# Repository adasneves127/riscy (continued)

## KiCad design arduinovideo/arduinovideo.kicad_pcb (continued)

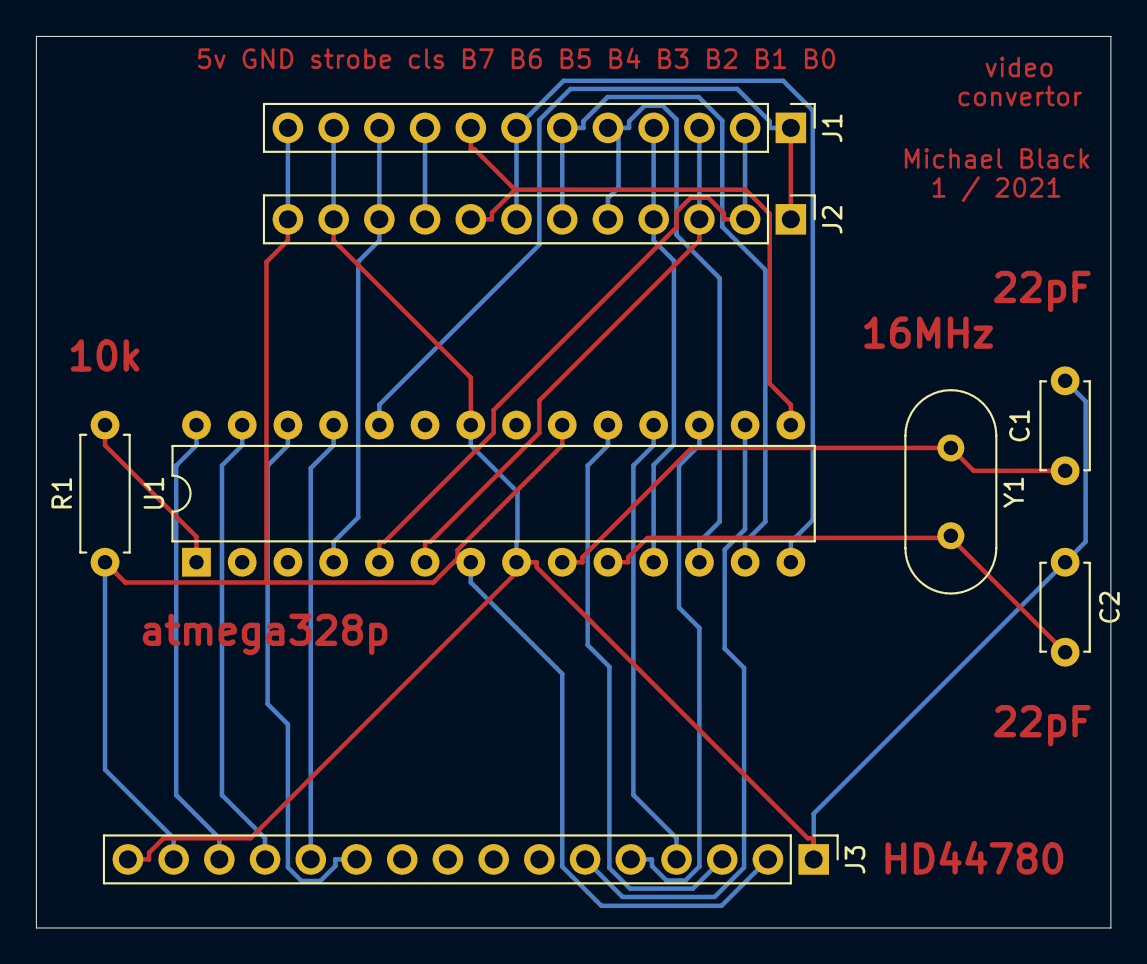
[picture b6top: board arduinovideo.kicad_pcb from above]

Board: 2 copper layers, 59.7 x 49.5 mm, 8 parts (0 on the bottom side), 23 nets.

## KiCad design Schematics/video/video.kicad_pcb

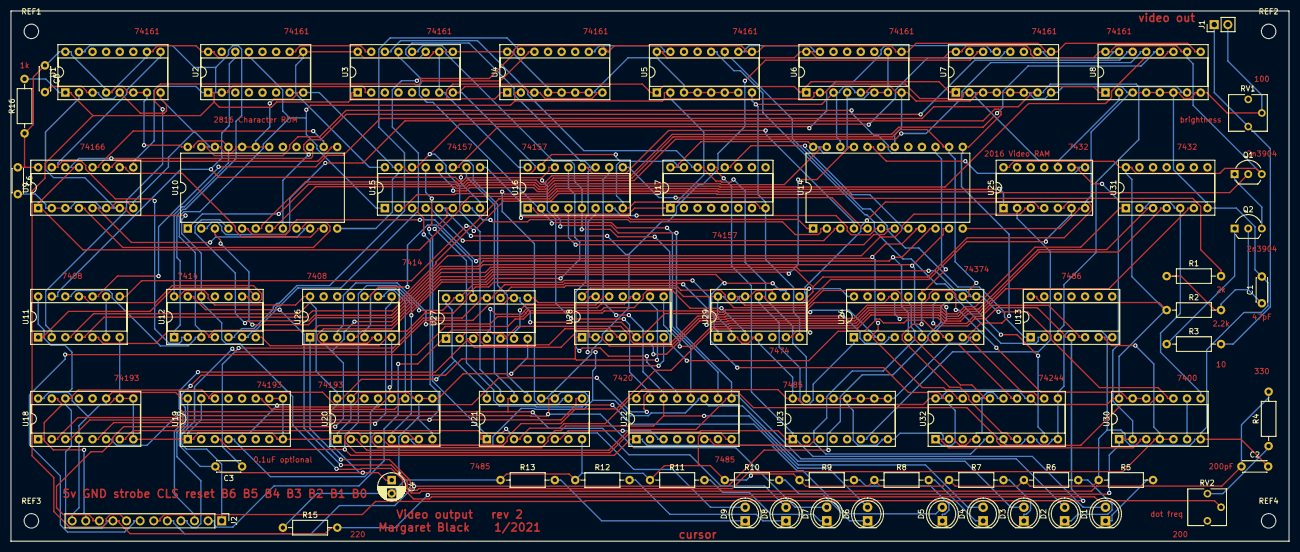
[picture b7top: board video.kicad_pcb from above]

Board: 2 copper layers, 238.8 x 99.1 mm, 72 parts (0 on the bottom side), 119 nets.

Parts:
C1: 47pF; C_Disc_D4.3mm_W1.9mm_P5.00mm
C2: 200pF; C_Disc_D4.3mm_W1.9mm_P5.00mm
C3, C5, C6: 0.1uF; C_Disc_D4.3mm_W1.9mm_P5.00mm
C4: CP; CP_Radial_D5.0mm_P2.50mm
D1, D2, D3, D4, D5, D6, D7, D8, D9: LED; LED_D5.0mm
J1: video_out; PinHeader_1x02_P2.54mm_Vertical
J2: Conn_01x12_Female; PinHeader_1x12_P2.54mm_Vertical
Q1, Q2: 2N3904; TO-92_Inline_Wide
R1: 2k; R_Axial_DIN0207_L6.3mm_D2.5mm_P10.16mm_Horizontal
R2: 2.2k; R_Axial_DIN0207_L6.3mm_D2.5mm_P10.16mm_Horizontal
R3: 10; R_Axial_DIN0207_L6.3mm_D2.5mm_P10.16mm_Horizontal
R4: 330; R_Axial_DIN0207_L6.3mm_D2.5mm_P10.16mm_Horizontal
R5, R6, R7, R8, R9, R10, R11, R12, R13, R16: 1k; R_Axial_DIN0207_L6.3mm_D2.5mm_P10.16mm_Horizontal
R15: 220; R_Axial_DIN0207_L6.3mm_D2.5mm_P10.16mm_Horizontal
REF1, REF2, REF3, REF4: MountingHole_2.7mm_M2.5
RV1: 100; Potentiometer_Vishay_T73YP_Vertical
RV2: 200; Potentiometer_Vishay_T73YP_Vertical
U1, U2, U3, U4, U5, U6, U7, U8: 74LS161; DIP-16_W7.62mm_Socket
U9: 74LS166; DIP-16_W7.62mm_Socket
U10: 2816; DIP-24_W15.24mm
U11, U26: 74LS08; DIP-14_W7.62mm_Socket
U12, U27: 74LS14; DIP-14_W7.62mm_Socket
U13: 74LS86; DIP-14_W7.62mm_Socket
U14: 2016; DIP-24_W15.24mm
U15, U16, U17: 74LS157; DIP-16_W7.62mm_Socket
U18, U19, U20: 74LS193; DIP-16_W7.62mm_Socket
U21, U22, U23: 74LS85; DIP-16_W7.62mm_Socket
U24: 74LS374; DIP-20_W7.62mm_Socket
U25, U31: 74LS32; DIP-14_W7.62mm_Socket
U28: 74LS20; DIP-14_W7.62mm_Socket
U29: 74LS74; DIP-14_W7.62mm_Socket
U30: 74LS00; DIP-14_W7.62mm_Socket
U32: 74LS244; DIP-20_W7.62mm_Socket

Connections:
+5V: C3.2, C4.1, C5.1, C6.1, J2.12, Q1.3, R2.1, R16.1, U1.4, U1.6, U1.7, U1.10, U1.16, U2.7, U2.9, U2.16, U3.7, U3.9, U3.10, U3.16, U4.4, U4.5, U4.6, U4.7, U4.16, U5.3, U5.4, U5.5, U5.6, U5.7, U5.16, U6.4, U6.6, U6.7, U6.10, U6.16, U7.16, U8.10, U8.16, U9.16, U10.21, U10.24, U11.14, U12.14, U13.14, U14.24, U15.16, U16.16, U17.16, U18.4, U18.11, U18.16, U19.16, U20.16, U21.3, U21.16, U22.16, U23.16, U24.20, U25.14, U26.14, U27.14, U28.14, U29.2, U29.4, U29.10, U29.12, U29.14, U30.14, U31.14, U32.13, U32.20
CLS: J2.9, R15.2, U18.14, U19.14, U20.14, U25.9, U30.1, U30.2
CR: U27.10, U30.12, U30.13
GND: C1.2, C2.2, C4.2, C5.2, C6.2, J1.2, J2.11, R5.1, R6.1, R7.1, R8.1, R9.1, R10.1, R11.1, R12.1, R13.1, R15.1, RV1.2, U1.3, U1.5, U1.8, U2.8, U3.8, U4.3, U4.8, U5.8, U6.3, U6.5, U6.8, U7.3, U7.4, U7.5, U7.6, U7.8, U8.3, U8.4, U8.5, U8.6, U8.8, U9.2, U9.3, U9.6, U9.8, U10.12, U10.18, U10.19, U10.20, U10.22, U11.7, U12.7, U13.7, U14.12, U14.18, U14.19, U14.22, U15.8, U15.15, U16.8, U16.15, U17.8, U17.15, U18.1, U18.8, U18.9, U18.10, U18.15, U19.1, U19.8, U19.9, U19.10, U19.15, U20.1, U20.8, U20.9, U20.10, U20.15, U21.8, U22.8, U23.8, U23.9, U23.10, U23.11, U23.12, U23.13, U23.14, U24.10, U25.7, U26.7, U27.7, U28.7, U29.7, U30.7, U31.7, U32.2, U32.4, U32.6, U32.8, U32.10, U32.11, U32.15, U32.17
H0: U3.14, U17.14, U23.15
H1: U3.13, U16.2, U22.10
H2: U3.12, U16.5, U22.12
H3: U3.11, U16.11, U22.13
H4: U2.14, U11.13, U16.14, U22.15
HACTIVE: U11.5, U12.4, U24.1, U25.5, U29.11
HBLANK: U11.1, U12.8
unnamed: C1.1, Q2.2, R1.1, R2.2
unnamed: C2.1, R4.2, U12.13
unnamed: C3.1, U27.11, U31.3
unnamed: D1.1, R5.2
unnamed: D2.1, R6.2
unnamed: D3.1, R7.2
unnamed: D4.1, R8.2
unnamed: D5.1, R9.2
unnamed: D6.1, R10.2
unnamed: D7.1, R11.2
unnamed: D8.1, R12.2
unnamed: D9.1, R13.2
unnamed: J1.1, R3.2, RV1.1
unnamed: Q1.1, Q2.3
unnamed: Q1.2, U11.3
unnamed: Q2.1, R3.1
unnamed: R4.1, RV2.3
unnamed: U1.9, U9.15, U12.2
unnamed: U1.15, U2.2, U3.2, U12.1
unnamed: U2.10, U3.15
unnamed: U4.10, U5.15
unnamed: U5.10, U6.15
unnamed: U7.10, U8.15
unnamed: U9.4, U10.9
unnamed: U9.5, U10.10
unnamed: U9.10, U10.11
unnamed: U9.11, U10.13
unnamed: U9.12, U10.14
unnamed: U9.14, U10.15
unnamed: U11.4, U25.3
unnamed: U11.6, U11.9
unnamed: U11.11, U12.9
unnamed: U4.15, U12.5
unnamed: U4.9, U5.9, U6.9, U7.9, U8.9, U12.6
unnamed: U5.11, U13.1
unnamed: U5.12, U13.2
unnamed: U13.6, U26.1, U30.4, U30.5
unnamed: U14.1, U15.9
unnamed: U14.2, U15.7
unnamed: U14.3, U15.4
unnamed: U14.4, U16.12
unnamed: U14.5, U16.9
unnamed: U14.6, U16.7
unnamed: U14.7, U16.4
unnamed: U14.8, U17.12
unnamed: U14.20, U25.8
unnamed: U14.23, U15.12
unnamed: U18.5, U26.8
unnamed: U19.4, U20.13
unnamed: U19.5, U20.12
unnamed: U19.11, U20.11, U26.9, U30.11
unnamed: U21.6, U22.3
unnamed: U22.6, U23.3
unnamed: U9.1, U9.13, U25.1
unnamed: U25.4, U29.6
unnamed: U25.6, U29.13
unnamed: U26.3, U29.3
unnamed: U26.4, U30.3, U32.1, U32.19
unnamed: U26.10, U27.12
unnamed: U27.2, U28.4
unnamed: U27.4, U28.10
unnamed: U27.6, U28.12
unnamed: U27.8, U28.13
unnamed: U28.6, U31.1
unnamed: U28.8, U31.4
unnamed: U30.6, U30.9
unnamed: U30.8, U31.2, U31.5
V0: U8.11, U15.2, U21.10
V1: U7.14, U15.5, U21.12
V2: U7.13, U15.11, U21.13
V3: U7.12, U15.14, U21.15
VACTIVE: U7.7, U8.7, U11.10, U13.3
VBLANK: U4.14, U11.2
char0: U10.5, U14.9, U24.2, U32.18
char1: U10.4, U14.10, U24.5, U32.16
char2: U10.3, U14.11, U24.6, U32.14
char3: U10.2, U14.13, U24.9, U32.12
char4: U10.1, U14.14, U24.12, U32.9
char5: U10.23, U14.15, U24.15, U32.7
char6: U24.16, U32.5
charin0: J2.1, U24.3, U27.9, U28.5
charin1: J2.2, U24.4, U27.1, U27.5
charin2: J2.3, U24.7, U27.3, U28.2
charin3: J2.4, U24.8, U28.1, U28.9
charin4: J2.5, U24.13
charin5: J2.6, U13.4, U24.14
charin6: J2.7, U13.5, U24.17
charinStrobe: J2.10, U24.11, U26.2, U30.10
charline0: U8.14, U10.8
charline1: U8.13, U10.7
charline2: U8.12, U10.6
cursorX0: D1.2, U17.13, U20.3, U23.1
cursorX1: D2.2, U16.3, U20.2, U22.9
cursorX2: D3.2, U16.6, U20.6, U22.11
cursorX3: D4.2, U16.10, U20.7, U22.14
cursorX4: D5.2, U16.13, U19.3, U22.1, U27.13
cursorY0: D6.2, U15.3, U18.3, U21.9
cursorY1: D7.2, U15.6, U18.2, U21.11
cursorY2: D8.2, U15.10, U18.6, U21.14
cursorY3: D9.2, U15.13, U18.7, U21.1
cursor_inc: U20.5, U26.5, U29.1, U29.9
dotclk: RV2.2, U1.2, U9.7, U12.12
reset: J2.8, R16.2, U1.1, U2.1, U3.1, U4.1, U5.1, U6.1, U7.1, U8.1, U9.9
videoAtCursor: U23.6, U25.2
video_shift: R1.2, U11.8
~BS: U20.4, U31.6
~HACTIVE: U2.13, U4.2, U5.2, U6.2, U7.2, U8.2, U11.12, U12.3, U15.1, U16.1, U17.1, U25.10
~vramWrite: U14.21, U26.6

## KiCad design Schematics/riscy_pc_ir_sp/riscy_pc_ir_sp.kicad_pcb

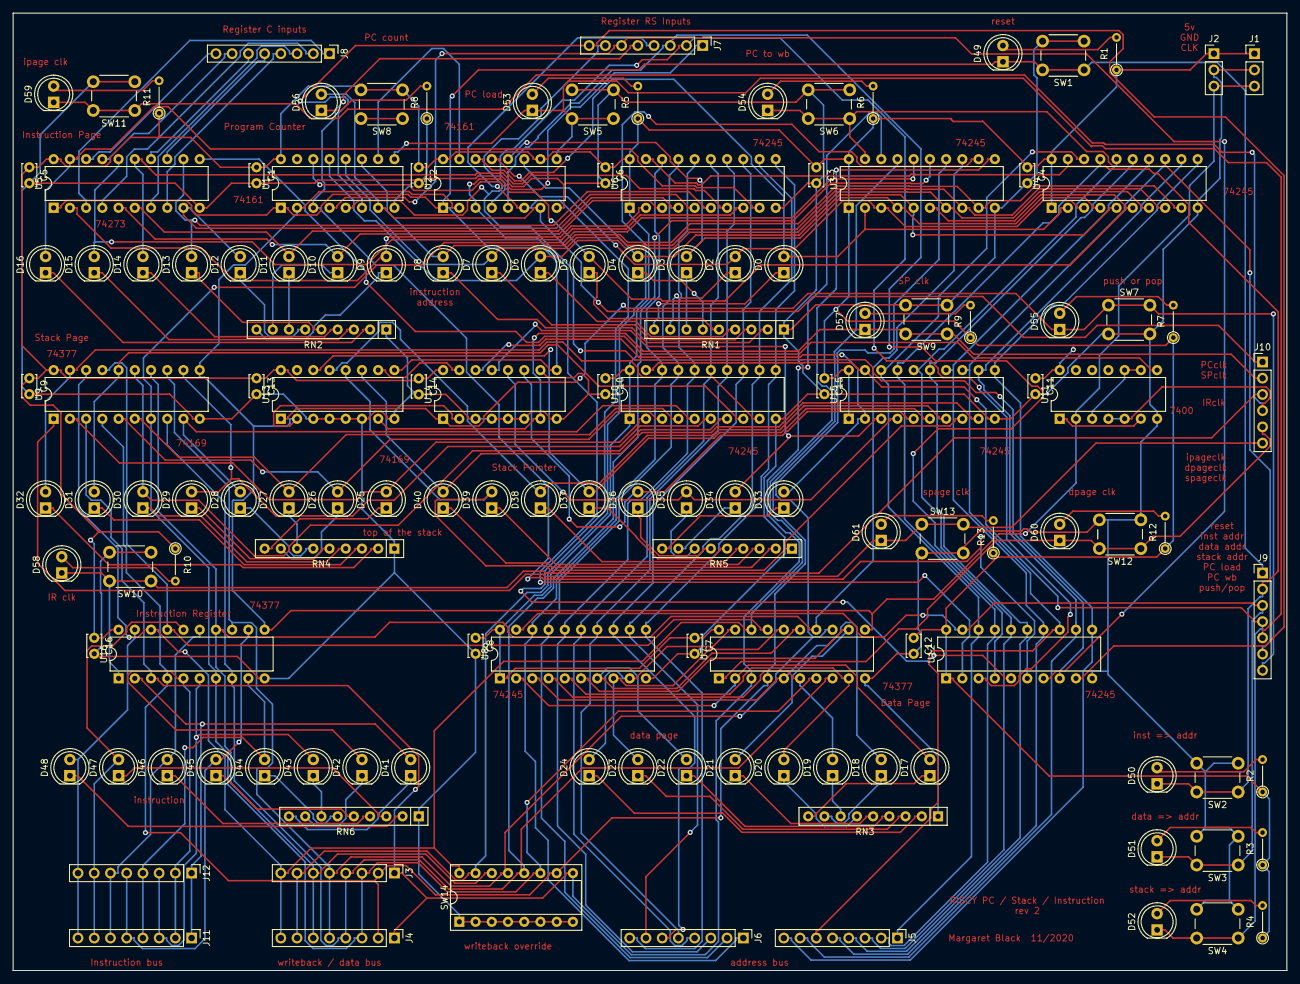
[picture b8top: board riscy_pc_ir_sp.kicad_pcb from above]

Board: 2 copper layers, 199.4 x 149.9 mm, 138 parts (0 on the bottom side), 170 nets.

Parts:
C1, C2, C3, C4, C5, C6, C7, C8, C9, C10, C11, C12, C13, C14, C15, C16: C; C_Disc_D3.4mm_W2.1mm_P2.50mm
D0, D2, D3, D4, D5, D6, D7, D8, D9, D10, D11, D12, D13, D14, D15, D16, D17, D18, D19, D20, D21, D22, D23, D24, D25, D26, D27, D28, D29, D30, D31, D32, D33, D34, D35, D36, D37, D38, D39, D40, D41, D42, D43, D44, D45, D46, D47, D48, D49, D50, D51, D52, D53, D54, D55, D56, D57, D58, D59, D60, D61: LED; LED_D5.0mm
J1, J2: Conn_01x03_Female; PinHeader_1x03_P2.54mm_Vertical
J3, J4, J5, J6, J7, J8, J11, J12: Conn_01x08_Female; PinHeader_1x08_P2.54mm_Vertical
J9: Conn_01x07_Female; PinHeader_1x07_P2.54mm_Vertical
J10: Conn_01x06_Female; PinHeader_1x06_P2.54mm_Vertical
R1, R2, R3, R4, R5, R6, R7, R8, R9, R10, R11, R12, R13: R; R_Axial_DIN0204_L3.6mm_D1.6mm_P5.08mm_Vertical
RN1, RN2, RN3, RN4, RN5, RN6: R_Network08; R_Array_SIP9
SW1, SW2, SW3, SW4, SW5, SW6, SW7, SW8, SW9, SW10, SW11, SW12, SW13: SW_Push; SW_PUSH_6mm
SW14: SW_DIP_x08; DIP-16_W7.62mm_Socket
U1, U2: 74LS161; DIP-16_W7.62mm
U3, U4, U6, U8, U10, U12, U15: 74LS245; DIP-20_W7.62mm
U5: 74LS273; DIP-20_W7.62mm
U7, U9, U16: 74LS377; DIP-20_W7.62mm
U11: 74LS00; DIP-14_W7.62mm
U13, U14: 74LS169; DIP-16_W7.62mm

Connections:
+5V: C1.1, C2.1, C3.1, C4.1, C5.1, C6.1, C7.1, C8.1, C9.1, C10.1, C11.1, C12.1, C13.1, C14.1, C15.1, C16.1, J1.1, J2.1, R1.1, R2.1, R3.1, R4.1, R5.1, R6.1, R7.1, R9.1, R10.1, R11.1, R12.1, R13.1, SW8.2, U1.16, U2.10, U2.16, U3.1, U3.20, U4.1, U4.20, U5.20, U6.1, U6.20, U7.20, U8.1, U8.20, U9.20, U10.1, U10.20, U11.14, U12.1, U12.20, U13.16, U14.16, U15.1, U15.20, U16.20
C0: J8.1, U5.3
C1: J8.2, U5.4
C2: J8.3, U5.7
C3: J8.4, U5.8
C4: J8.5, U5.13
C5: J8.6, U5.14
C6: J8.7, U5.17
C7: J8.8, U5.18
CLK: J1.3, J2.3, U1.2, U2.2, U7.11, U9.11, U11.2, U13.2, U14.2, U16.11
GND: C1.2, C2.2, C3.2, C4.2, C5.2, C6.2, C7.2, C8.2, C9.2, C10.2, C11.2, C12.2, C13.2, C14.2, C15.2, C16.2, J1.2, J2.2, R8.1, RN1.1, RN2.1, RN3.1, RN4.1, RN5.1, RN6.1, SW1.2, SW2.2, SW3.2, SW4.2, SW5.2, SW6.2, SW7.2, SW9.2, SW10.2, SW11.2, SW12.2, SW13.2, SW14.1, SW14.2, SW14.3, SW14.4, SW14.5, SW14.6, SW14.7, SW14.8, U1.8, U2.8, U3.10, U4.10, U5.10, U6.10, U7.10, U8.10, U9.10, U10.10, U11.7, U12.10, U13.3, U13.4, U13.5, U13.6, U13.8, U14.3, U14.4, U14.5, U14.6, U14.8, U14.10, U15.10, U16.10
IRclk: D58.1, J10.3, SW10.1, U16.1
unnamed: D0.1, RN1.9
unnamed: D0.2, U2.14, U3.2, U4.2
unnamed: D2.1, RN1.8
unnamed: D2.2, U2.13, U3.3, U4.3
unnamed: D3.1, RN1.7
unnamed: D3.2, U2.12, U3.4, U4.4
unnamed: D4.1, RN1.6
unnamed: D4.2, U2.11, U3.5, U4.5
unnamed: D5.1, RN1.5
unnamed: D5.2, U1.14, U3.6, U4.6
unnamed: D6.1, RN1.4
unnamed: D6.2, U1.13, U3.7, U4.7
unnamed: D7.1, RN1.3
unnamed: D7.2, U1.12, U3.8, U4.8
unnamed: D8.1, RN1.2
unnamed: D8.2, U1.11, U3.9, U4.9
unnamed: D9.1, RN2.9
unnamed: D9.2, U5.2, U6.2
unnamed: D10.1, RN2.8
unnamed: D10.2, U5.5, U6.3
unnamed: D11.1, RN2.7
unnamed: D11.2, U5.6, U6.4
unnamed: D12.1, RN2.6
unnamed: D12.2, U5.9, U6.5
unnamed: D13.1, RN2.5
unnamed: D13.2, U5.12, U6.6
unnamed: D14.1, RN2.4
unnamed: D14.2, U5.15, U6.7
unnamed: D15.1, RN2.3
unnamed: D15.2, U5.16, U6.8
unnamed: D16.1, RN2.2
unnamed: D16.2, U5.19, U6.9
unnamed: D17.1, RN3.9
unnamed: D17.2, U7.2, U8.2
unnamed: D18.1, RN3.8
unnamed: D18.2, U7.5, U8.3
unnamed: D19.1, RN3.7
unnamed: D19.2, U7.6, U8.4
unnamed: D20.1, RN3.6
unnamed: D20.2, U7.9, U8.5
unnamed: D21.1, RN3.5
unnamed: D21.2, U7.12, U8.6
unnamed: D22.1, RN3.4
unnamed: D22.2, U7.15, U8.7
unnamed: D23.1, RN3.3
unnamed: D23.2, U7.16, U8.8
unnamed: D24.1, RN3.2
unnamed: D24.2, U7.19, U8.9
unnamed: D25.1, RN4.9
unnamed: D25.2, U9.2, U10.2
unnamed: D26.1, RN4.8
unnamed: D26.2, U9.5, U10.3
unnamed: D27.1, RN4.7
unnamed: D27.2, U9.6, U10.4
unnamed: D28.1, RN4.6
unnamed: D28.2, U9.9, U10.5
unnamed: D29.1, RN4.5
unnamed: D29.2, U9.12, U10.6
unnamed: D30.1, RN4.4
unnamed: D30.2, U9.15, U10.7
unnamed: D31.1, RN4.3
unnamed: D31.2, U9.16, U10.8
unnamed: D32.1, RN4.2
unnamed: D32.2, U9.19, U10.9
unnamed: D33.1, RN5.9
unnamed: D33.2, U14.14, U15.2
unnamed: D34.1, RN5.8
unnamed: D34.2, U14.13, U15.3
unnamed: D35.1, RN5.7
unnamed: D35.2, U14.12, U15.4
unnamed: D36.1, RN5.6
unnamed: D36.2, U14.11, U15.5
unnamed: D37.1, RN5.5
unnamed: D37.2, U13.14, U15.6
unnamed: D38.1, RN5.4
unnamed: D38.2, U13.13, U15.7
unnamed: D39.1, RN5.3
unnamed: D39.2, U13.12, U15.8
unnamed: D40.1, RN5.2
unnamed: D40.2, U13.11, U15.9
unnamed: D41.1, RN6.9
unnamed: D42.1, RN6.8
unnamed: D43.1, RN6.7
unnamed: D44.1, RN6.6
unnamed: D45.1, RN6.5
unnamed: D46.1, RN6.4
unnamed: D47.1, RN6.3
unnamed: D48.1, RN6.2
unnamed: D49.2, R1.2
unnamed: D50.2, R2.2
unnamed: D51.2, R3.2
unnamed: D52.2, R4.2
unnamed: D53.2, R5.2
unnamed: D54.2, R6.2
unnamed: D55.2, R7.2
unnamed: D56.1, R8.2
unnamed: D57.2, R9.2
unnamed: D58.2, R10.2
unnamed: D59.2, R11.2
unnamed: D60.2, R12.2
unnamed: D61.2, R13.2
unnamed: U1.10, U2.15
unnamed: U11.1, U11.6
unnamed: U5.11, U11.8
unnamed: U11.3, U11.9, U11.10
unnamed: U13.10, U14.15
PCaddr: D50.1, J9.2, SW2.1, U4.19, U6.19
PCclk: D56.2, J10.1, SW8.1, U1.7, U2.7
PCload: D53.1, J9.5, SW5.1, U1.9, U2.9
PCwb: D54.1, J9.6, SW6.1, U3.19
Rrs0: J7.1, U2.3, U12.2
Rrs1: J7.2, U2.4, U12.3
Rrs2: J7.3, U2.5, U12.4
Rrs3: J7.4, U2.6, U12.5
Rrs4: J7.5, U1.3, U12.6
Rrs5: J7.6, U1.4, U12.7
Rrs6: J7.7, U1.5, U12.8
Rrs7: J7.8, U1.6, U12.9
Rrsaddr: D51.1, J9.3, SW3.1, U8.19, U12.19
SPaddr: D52.1, J9.4, SW4.1, U10.19, U15.19
SPclk: D57.1, J10.2, SW9.1, U13.7, U14.7
addr0: J5.1, U4.18, U12.18, U15.18
addr1: J5.2, U4.17, U12.17, U15.17
addr2: J5.3, U4.16, U12.16, U15.16
addr3: J5.4, U4.15, U12.15, U15.15
addr4: J5.5, U4.14, U12.14, U15.14
addr5: J5.6, U4.13, U12.13, U15.13
addr6: J5.7, U4.12, U12.12, U15.12
addr7: J5.8, U4.11, U12.11, U15.11
addr8: J6.1, U6.18, U8.18, U10.18
addr9: J6.2, U6.17, U8.17, U10.17
addr10: J6.3, U6.16, U8.16, U10.16
addr11: J6.4, U6.15, U8.15, U10.15
addr12: J6.5, U6.14, U8.14, U10.14
addr13: J6.6, U6.13, U8.13, U10.13
addr14: J6.7, U6.12, U8.12, U10.12
addr15: J6.8, U6.11, U8.11, U10.11
dpageclk: D60.1, J10.5, SW12.1, U7.1
ipageclk: D59.1, J10.4, SW11.1, U11.4, U11.5
ir0: D41.2, J11.1, J12.1, U16.2
ir1: D42.2, J11.2, J12.2, U16.5
ir2: D43.2, J11.3, J12.3, U16.6
ir3: D44.2, J11.4, J12.4, U16.9
ir4: D45.2, J11.5, J12.5, U16.12
ir5: D46.2, J11.6, J12.6, U16.15
ir6: D47.2, J11.7, J12.7, U16.16
ir7: D48.2, J11.8, J12.8, U16.19
pushpop: D55.1, J9.7, SW7.1, U13.1, U14.1
reset: D49.1, J9.1, SW1.1, U1.1, U2.1, U5.1, U13.9, U14.9
spageclk: D61.1, J10.6, SW13.1, U9.1
wb0: J3.1, J4.1, SW14.9, U3.18, U7.3, U9.3, U16.3
wb1: J3.2, J4.2, SW14.10, U3.17, U7.4, U9.4, U16.4
wb2: J3.3, J4.3, SW14.11, U3.16, U7.7, U9.7, U16.7
wb3: J3.4, J4.4, SW14.12, U3.15, U7.8, U9.8, U16.8
wb4: J3.5, J4.5, SW14.13, U3.14, U7.13, U9.13, U16.13
wb5: J3.6, J4.6, SW14.14, U3.13, U7.14, U9.14, U16.14
wb6: J3.7, J4.7, SW14.15, U3.12, U7.17, U9.17, U16.17
wb7: J3.8, J4.8, SW14.16, U3.11, U7.18, U9.18, U16.18

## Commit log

2021-01-23 initial riscy
2021-01-24 RISCY with tinybasic
2022-03-08 3/8/22
2022-10-13 Added GitIgnore
2022-10-13 More Gitignore
2022-12-07 Interim
2023-01-08 Updated Gitignore
2023-01-08 Finished Organization
